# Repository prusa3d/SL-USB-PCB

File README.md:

# PRUSA SL-USB board

KiCad PCB layout

* [Interactive bom](http://htmlpreview.github.io/?https://github.com/prusa3d/SL-USB-PCB/blob/master/rev.02/ibom.html)
* [STEP 3D model](rev.02/SL-USB-02.step)

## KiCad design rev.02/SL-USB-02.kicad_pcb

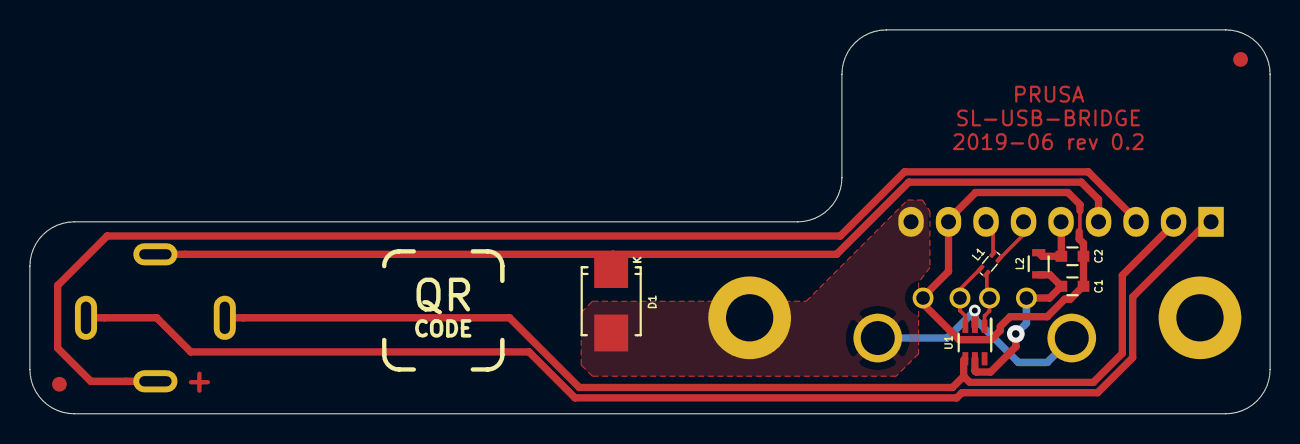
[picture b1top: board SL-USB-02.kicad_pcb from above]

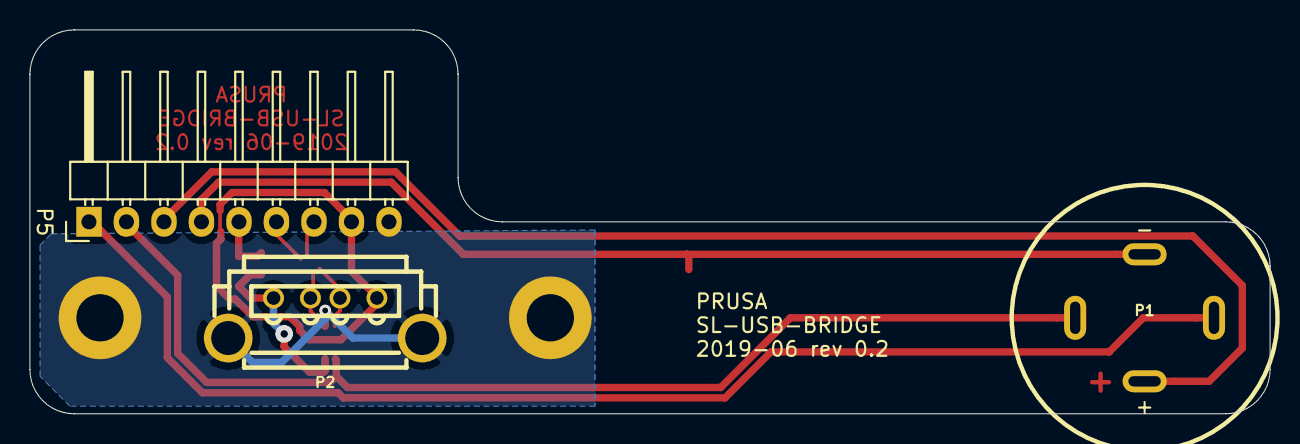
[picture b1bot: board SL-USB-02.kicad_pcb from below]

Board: 2 copper layers, 84.0 x 26.0 mm, 14 parts (3 on the bottom side), 12 nets.

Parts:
C1, C2: 100n; C_0603
D1: SMBJ24A; SMB_Standard
L1: 0603USB-601MLB; 0603USB-common-mode
L2: BLM18KG121TN1D; R_0603
MK1, MK2: Fiducial; Fiducial_1mm_Dia_2.54mm_Outer_CopperTop
P1: PWR-button*; ONPOW-LED-BUTTON
P2: USB-A; USB-A-S-VT_ADAM-TECH
P3, P4: CONN_01X01*; MountingHole_3.2mm_M3_DIN965_Pad
P5: 70553-0043; Pin_Header_Angled_1x09
Q1: QR-code*; QR-code-8x8mm
U1: NUP4202; SC-88

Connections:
unnamed: C1.1, L2.1, P2.1, U1.5
unnamed: C1.2, C2.2, P2.4, P5.8
unnamed: C2.1, L2.2, P5.5
unnamed: D1.1, P1.4, P5.4
unnamed: D1.2, P2.5, P3.1, P4.1, P5.9, U1.2
unnamed: L1.1, P2.2, U1.1
unnamed: L1.2, P5.6
unnamed: L1.3, P5.7
unnamed: L1.4, P2.3, U1.3
unnamed: P1.1, P5.1
unnamed: P1.2, P5.2, U1.4
unnamed: P1.3, P5.3
